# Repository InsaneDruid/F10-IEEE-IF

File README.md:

# F10-IEEE-IF - a CBM6400 / StarWriter F10 IEEE-488 interface clone
A 100% compatible replica of the F10-IEEE-IF IEEE-488 internal interface board used in the CBM 6400 daisy-wheel printer to convert the parallel interface of its StarWriter F10-based internals to the IEEE-488 bus used in the CBM PET series computers. 

[Schematic](https://github.com/InsaneDruid/F10-IEEE-IF/blob/main/F10-IEEE-IF.pdf "Schematic")  

[Bill of Materials](https://htmlpreview.github.io/?https://github.com/InsaneDruid/F10-IEEE-IF/blob/main/bom/F10-IEEE-IF_bom.html "Bill of Materials")

## The IEEE-488 device number
There are 4 jumpers on the interface card that define the device number under which the printer can be accessed.
Set them according to the table:

| device number | J1 | J2 | J3 | J4 |
|---------------|----|----|----|----|
| 1             | 1  | 0  | 0  | 0  |
| 2             | 0  | 1  | 0  | 0  |
| 3             | 1  | 1  | 0  | 0  |
| 4 (default)   | 0  | 0  | 1  | 0  |
| 5             | 1  | 0  | 1  | 0  |
| 6             | 0  | 1  | 1  | 0  |
| 7             | 1  | 1  | 1  | 0  |
| 8             | 0  | 0  | 0  | 1  |
| 9             | 1  | 0  | 0  | 1  |
| 10            | 0  | 1  | 0  | 1  |
| 11            | 1  | 1  | 0  | 1  |
| 12            | 0  | 0  | 1  | 1  |
| 13            | 1  | 0  | 1  | 1  |
| 14            | 0  | 1  | 1  | 1  |
| 15            | 1  | 1  | 1  | 1  |

## The License
This work is licensed under a Creative Commons Attribution-ShareAlike 4.0 International License.   
See https://creativecommons.org/licenses/by-sa/4.0/.

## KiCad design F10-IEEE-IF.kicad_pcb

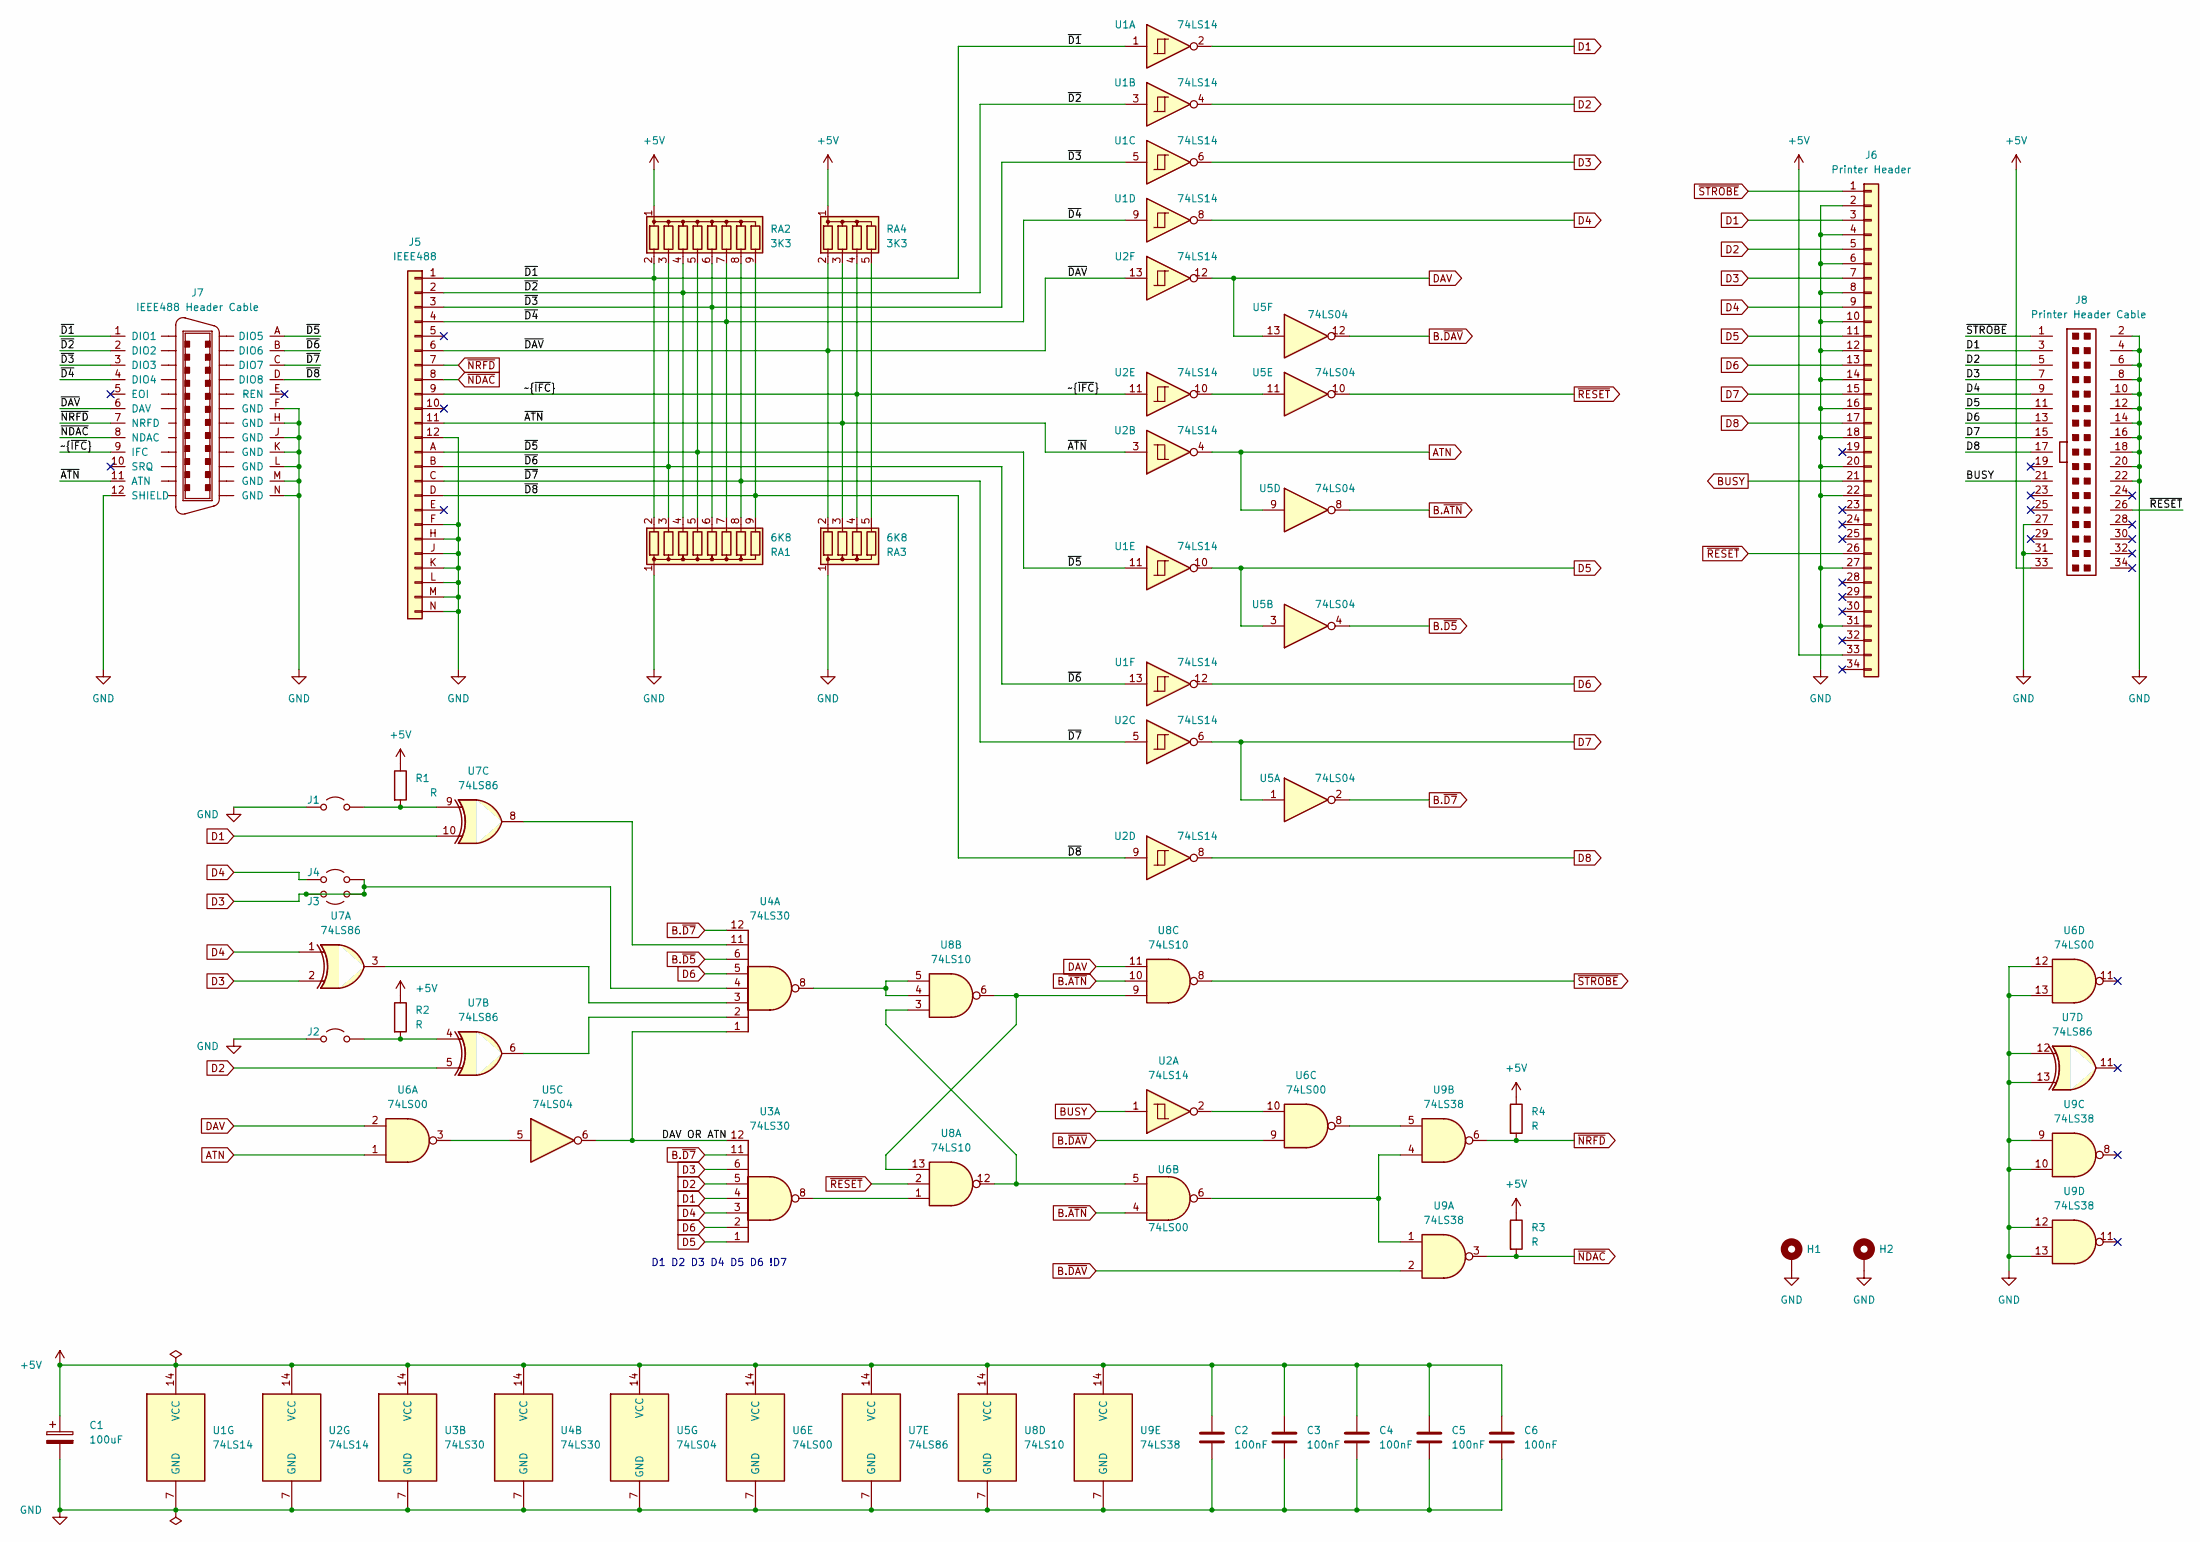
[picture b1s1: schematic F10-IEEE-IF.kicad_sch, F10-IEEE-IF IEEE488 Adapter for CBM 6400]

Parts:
C1: 100uF; CP_Axial_L11.0mm_D5.0mm_P20.32mm_Horizontal
C2, C3, C4, C5, C6: 100nF; C_Disc_D4.3mm_W1.9mm_P5.00mm
H1: MountingHole_Pad; MountingHole_2.5mm_Pad
H2: MountingHole_Pad; MountingHole_2.5mm_Pad_Slot
J1, J2, J3, J4: Jumper_2_Open; Jumper_Wire
J5: IEEE488; IDC-Header_2x12_P2.54mm_Vertical
J6: Printer Header; IDC-Header_2x17_P2.54mm_Vertical
J7: IEEE488 Header Cable; centronix-24-female
J8: Printer Header Cable
R1, R2, R3, R4: R; R_Axial_DIN0207_L6.3mm_D2.5mm_P10.16mm_Horizontal
RA1: 6K8; R_Array_SIP9
RA2: 3K3; R_Array_SIP9
RA3: 6K8; R_Array_SIP5
RA4: 3K3; R_Array_SIP5
U1, U2: 74LS14; DIP-14_W7.62mm
U3, U4: 74LS30; DIP-14_W7.62mm
U5: 74LS04; DIP-14_W7.62mm
U6: 74LS00; DIP-14_W7.62mm
U7: 74LS86; DIP-14_W7.62mm
U8: 74LS10; DIP-14_W7.62mm
U9: 74LS38; DIP-14_W7.62mm

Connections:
+5V: C1.1, C2.1, C3.1, C4.1, C5.1, C6.1, J6.33, J8.33, R1.1, R2.1, R3.1, R4.1, RA2.1 (common), RA4.1 (common), U1.14 (VCC), U2.14 (VCC), U3.14 (VCC), U4.14 (VCC), U5.14 (VCC), U6.14 (VCC), U7.14 (VCC), U8.14 (VCC), U9.14 (VCC)
/DAV OR ATN: U3.12, U4.1, U5.6
/~ATN: J5.11 (ATN), J7.11 (ATN), RA3.3 (R2), RA4.3 (R2), U2.3
/~D1: J5.1 (DIO1), J7.1 (DIO1), RA1.2 (R1), RA2.2 (R1), U1.1
/~D2: J5.2 (DIO2), J7.2 (DIO2), RA1.4 (R3), RA2.4 (R3), U1.3
/~D3: J5.3 (DIO3), J7.3 (DIO3), RA1.6 (R5), RA2.6 (R5), U1.5
/~D4: J5.4 (DIO4), J7.4 (DIO4), RA1.7 (R6), RA2.7 (R6), U1.9
/~D5: J5.A (DIO5), J7.A (DIO5), RA1.5 (R4), RA2.5 (R4), U1.11
/~D6: J5.B (DIO6), J7.B (DIO6), RA1.3 (R2), RA2.3 (R2), U1.13
/~D7: J5.C (DIO7), J7.C (DIO7), RA1.8 (R7), RA2.8 (R7), U2.5
/~D8: J5.D (DIO8), J7.D (DIO8), RA1.9 (R8), RA2.9 (R8), U2.9
/~DAV: J5.6 (DAV), J7.6 (DAV), RA3.2 (R1), RA4.2 (R1), U2.13
/~~{IFC}: J5.9 (IFC), J7.9 (IFC), RA3.4 (R3), RA4.4 (R3), U2.11
ATN: U2.4, U5.9, U6.1
B.~ATN: U5.8, U6.4, U8.10
B.~D5: U4.6, U5.4
B.~D7: U3.11, U4.12, U5.2
B.~DAV: U5.12, U6.9, U9.2
BUSY: J6.21, U2.1
D1: J6.3, U1.2, U3.4, U7.10
D2: J6.5, U1.4, U3.5, U7.5
D3: J3.1 (A), J3.2 (B), J4.2 (B), J6.7, U1.6, U3.6, U4.4, U7.2
D4: J4.1 (A), J6.9, U1.8, U3.3, U7.1
D5: J6.11, U1.10, U3.1, U5.3
D6: J6.13, U1.12, U3.2, U4.5
D7: J6.15, U2.6, U5.1
D8: J6.17, U2.8
DAV: U2.12, U5.13, U6.2, U8.11
GND: C1.2, C2.2, C3.2, C4.2, C5.2, C6.2, H1.1, H2.1, J1.1 (A), J2.1 (A), J5.12 (SHIELD), J5.F (GND), J5.H (GND), J5.J (GND), J5.K (GND), J5.L (GND), J5.M (GND), J5.N (GND), J6.2, J6.4, J6.6, J6.8, J6.10, J6.12, J6.14, J6.16, J6.18, J6.20, J6.22, J6.27, J6.31, J7.12 (SHIELD), J7.F (GND), J7.H (GND), J7.J (GND), J7.K (GND), J7.L (GND), J7.M (GND), J7.N (GND), J8.2, J8.4, J8.6, J8.8, J8.10, J8.12, J8.14, J8.16, J8.18, J8.20, J8.22, J8.27, J8.31, RA1.1 (common), RA3.1 (common), U1.7 (GND), U2.7 (GND), U3.7 (GND), U4.7 (GND), U5.7 (GND), U6.7 (GND), U6.12, U6.13, U7.7 (GND), U7.12, U7.13, U8.7 (GND), U9.7 (GND), U9.9, U9.10, U9.12, U9.13
unnamed: J1.2 (B), R1.2, U7.9
unnamed: J2.2 (B), R2.2, U7.4
unnamed: RA3.5 (R4), RA4.5 (R4)
unnamed: U2.2, U6.10
unnamed: U2.10, U5.11
unnamed: U3.8, U8.1
unnamed: U4.2, U7.6
unnamed: U4.3, U7.3
unnamed: U4.8, U8.4, U8.5
unnamed: U4.11, U7.8
unnamed: U5.5, U6.3
unnamed: U6.5, U8.3, U8.12
unnamed: U6.6, U9.1, U9.4
unnamed: U6.8, U9.5
unnamed: U8.6, U8.9, U8.13
~NDAC: J5.8 (NDAC), R3.2, U9.3
~NRFD: J5.7 (NRFD), R4.2, U9.6
~RESET: J6.26, U5.10, U8.2
~STROBE: J6.1, U8.8

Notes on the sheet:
D1 D2 D3 D4 D5 D6 !D7

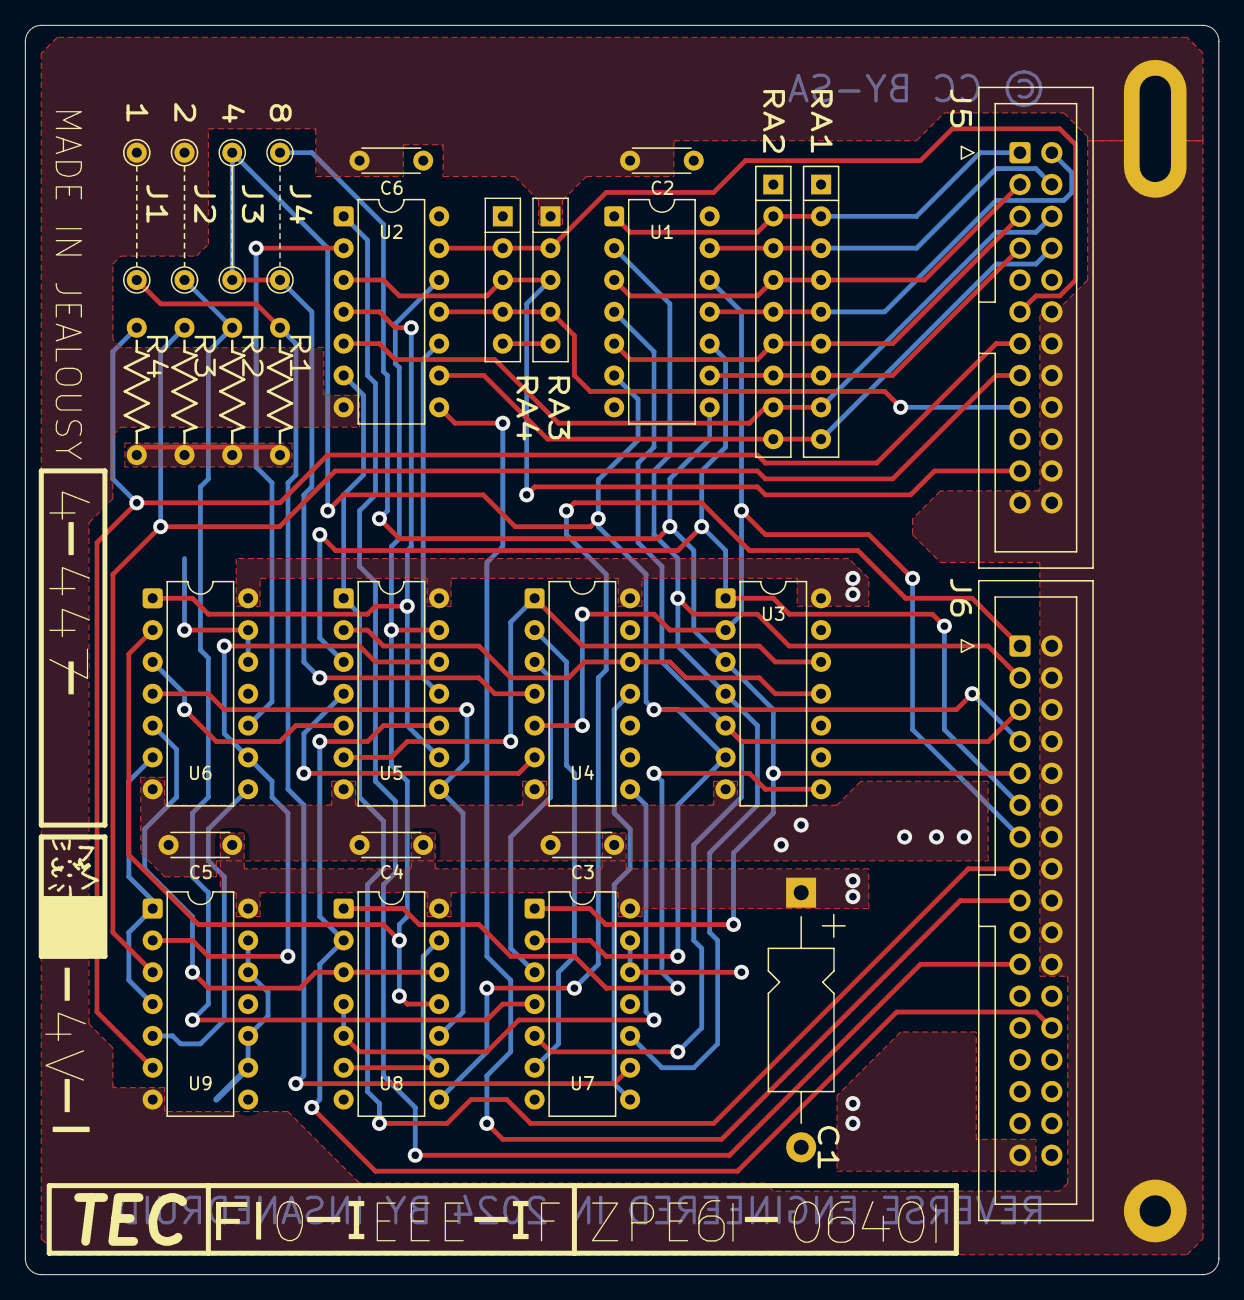
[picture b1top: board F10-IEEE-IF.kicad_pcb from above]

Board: 2 copper layers, 95.2 x 99.7 mm, 31 parts (0 on the bottom side), 48 nets.

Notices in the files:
F10-IEEE-IF.kicad_pcb:
License: CC BY-SA 4.0
© CC BY-SA
